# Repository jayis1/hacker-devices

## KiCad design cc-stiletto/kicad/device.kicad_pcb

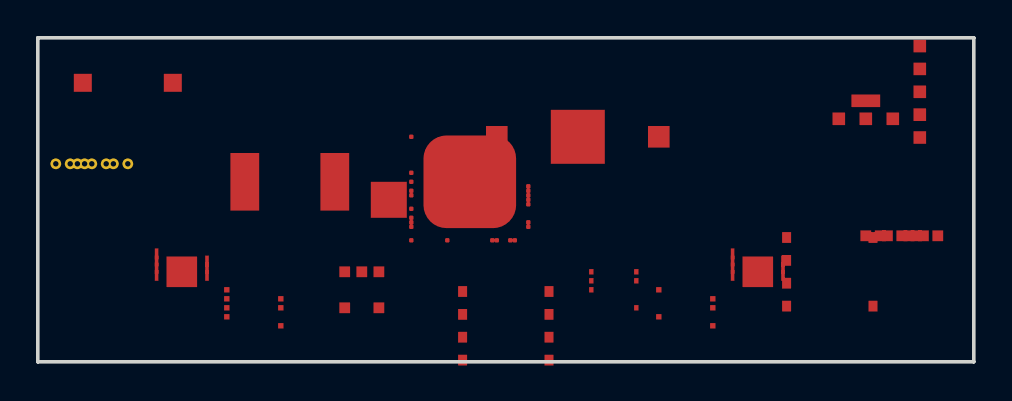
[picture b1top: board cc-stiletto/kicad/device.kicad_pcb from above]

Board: 0 copper layers, 52.0 x 18.0 mm, 17 parts (0 on the bottom side), 29 nets, no tracks yet.

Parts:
C_BULK: 100uF 50V; CP_Elec_6.3x7.7
D1: Status RGB LED; LED_RGB_1210
J1: USB-C Plug (victim/DUT); USB_C_Plug_Molex_105444
J2: USB-C Receptacle (source/host); USB_C_Receptacle_Amphenol_12401610E4-2A
J3: Pogo SWD debug; PinHeader_1x05_P1.27mm_Vertical
Q1: IPK95N04L; TO-263-3_TabPin2
R_SHUNT1: 5mR 1% 3W; R_2512_6332Metric
SW1: Mode/Hard-Reset button; SW_SPST_B3SN-6x6
U1: STM32G474CEU6; QFN-48-1EP_7x7mm_P0.5mm_EP5.15x5.15mm
U2, U3: FUSB302BMPX; QFN-14-1EP_3x3mm_P0.4mm_EP1.7x1.7mm
U4: LM5180-1W; SOT-23-6
U5: TPS25940; QFN-16-1EP_3x3mm_P0.5mm
U6: MAX5370; SOIC-14_3.9x8.7mm_P1.27mm
U7, U8: INA226; VSSOP-10_3x3mm_P0.5mm
U9: ISO1540; SOIC-8_3.9x4.9mm_P1.27mm

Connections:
BUTTON: SW1.1, U1.19
CC1_SNK: J2.A5, U3.2
CC1_SRC: J1.A5, U2.2
CC2_SNK: J2.B5, U3.3
CC2_SRC: J1.B5, U2.3
DAC_ILIM: U5.3, U6.2
GND: C_BULK.2, D1.4, J1.A1, J1.B1, J2.A1, J2.B1, J3.3, SW1.2, U1.5, U1.33, U1.EXP, U2.4, U2.14, U3.4, U3.14, U4.2, U4.5, U5.6, U6.7, U7.4, U8.4, U9.3, U9.6
HRTIM_CHA1: Q1.1, U1.29
I2C1_SCL: U1.42, U2.9
I2C1_SDA: U1.43, U2.8
I2C2_SDA: U1.30, U3.8
I2C3_SCL: U1.9, U6.6, U7.9, U8.9, U9.2, U9.8
I2C3_SDA: U1.10, U6.5, U7.8, U8.8, U9.1, U9.7
INT_SNK: U1.38, U3.10
INT_SRC: U1.20, U2.10
LED_B: D1.3, U1.16
LED_G: D1.2, U1.15
LED_R: D1.1, U1.14
NRST: J3.5, U1.7
SHUNT_SRC: J1.A4, J1.B4, R_SHUNT1.1, U7.2
SHUNT_SRC_OUT: R_SHUNT1.2, U5.1, U7.3
SWCLK: J3.2, U1.37
SWDIO: J3.1, U1.34
USB_DM: J1.A6, J2.A6, U1.46
USB_DP: J1.A7, J2.A7, U1.45
VBUS_SNK: J2.A4, J2.B4, Q1.2, U3.1, U5.2, U8.1
VBUS_SRC: C_BULK.1, Q1.3, U2.1, U4.1, U4.3, U7.1
VDD_3V3: J3.4, U1.1, U1.13, U6.14, U7.10, U8.10, U9.4
VDD_5V_ISO: U4.4, U9.5

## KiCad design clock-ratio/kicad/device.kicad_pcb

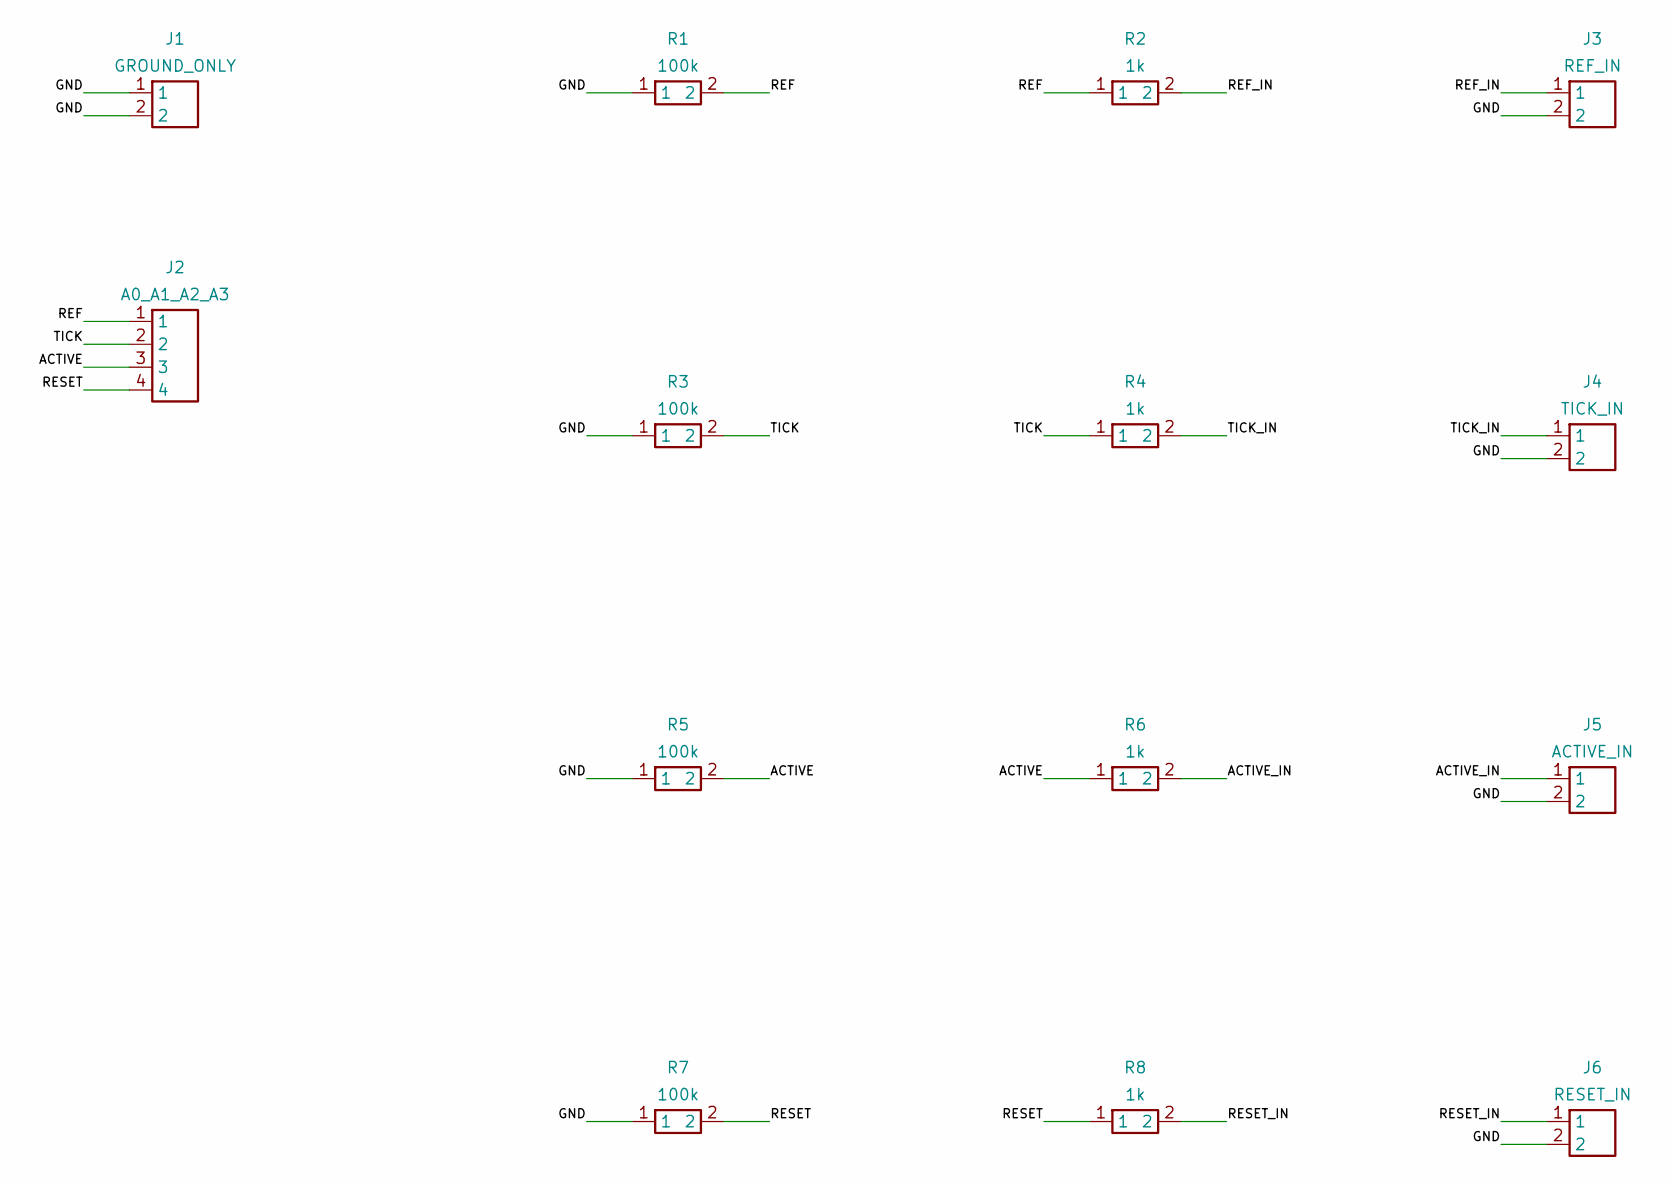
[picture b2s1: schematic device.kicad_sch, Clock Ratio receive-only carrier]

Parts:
J1: GROUND_ONLY; PinHeader_1x02_P2.54mm_Vertical
J2: A0_A1_A2_A3; PinHeader_1x04_P2.54mm_Vertical
J3: REF_IN; PinHeader_1x02_P2.54mm_Vertical
J4: TICK_IN; PinHeader_1x02_P2.54mm_Vertical
J5: ACTIVE_IN; PinHeader_1x02_P2.54mm_Vertical
J6: RESET_IN; PinHeader_1x02_P2.54mm_Vertical
R1, R3, R5, R7: 100k; R_Axial_DIN0207_L6.3mm_D2.5mm_P7.62mm_Horizontal
R2, R4, R6, R8: 1k; R_Axial_DIN0207_L6.3mm_D2.5mm_P7.62mm_Horizontal

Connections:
ACTIVE: J2.3, R5.2, R6.1
ACTIVE_IN: J5.1, R6.2
GND: J1.1, J1.2, J3.2, J4.2, J5.2, J6.2, R1.1, R3.1, R5.1, R7.1
REF: J2.1, R1.2, R2.1
REF_IN: J3.1, R2.2
RESET: J2.4, R7.2, R8.1
RESET_IN: J6.1, R8.2
TICK: J2.2, R3.2, R4.1
TICK_IN: J4.1, R4.2

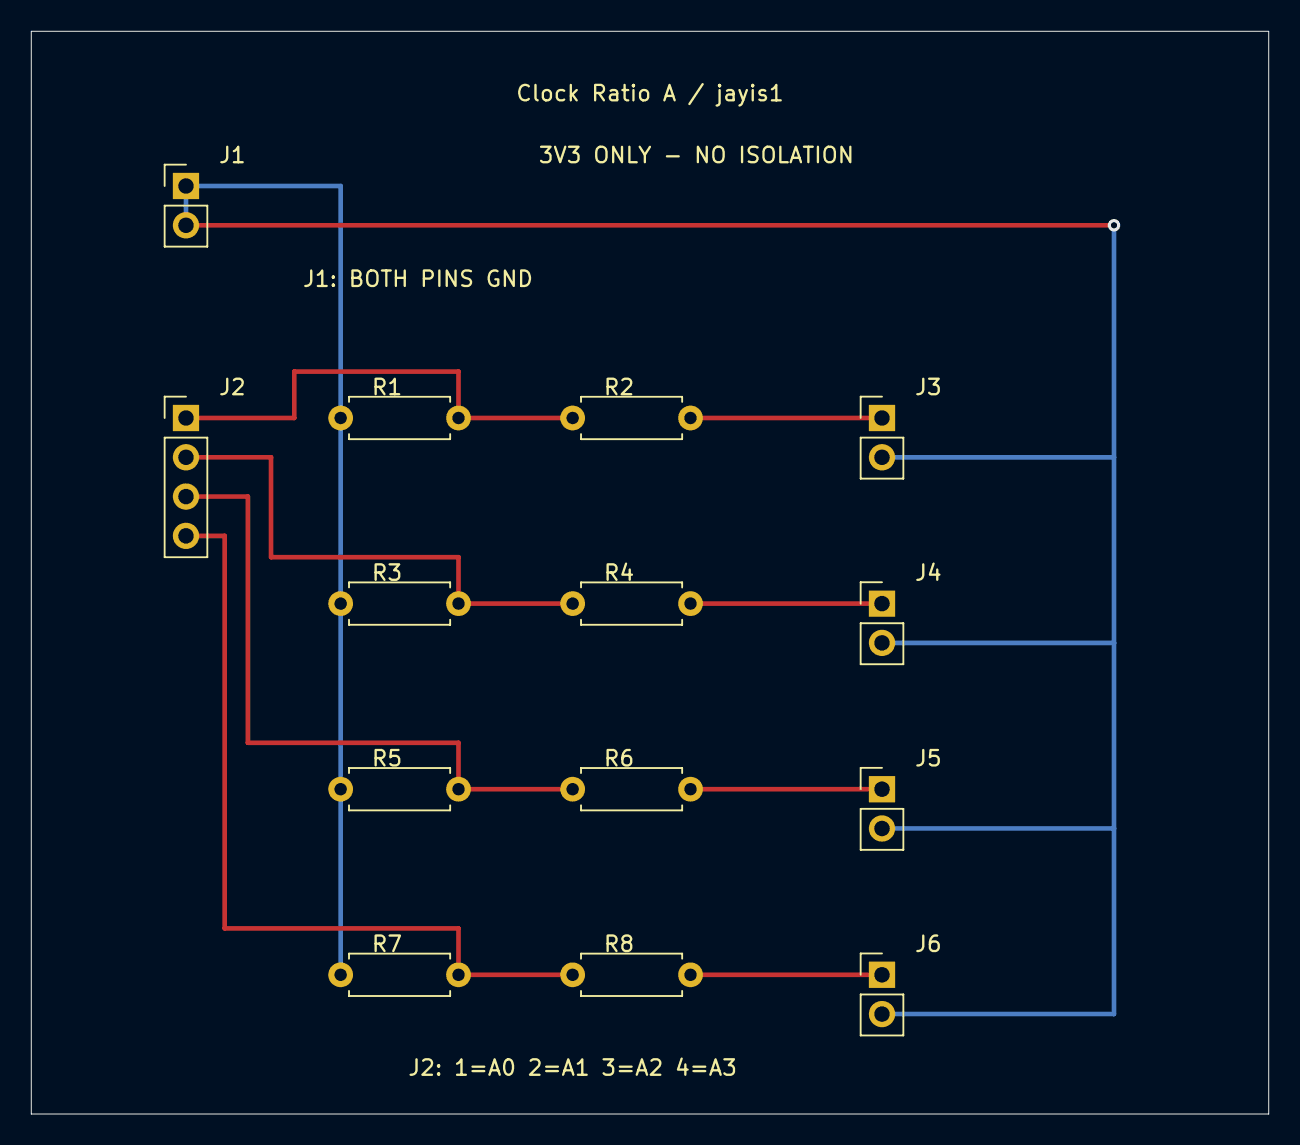
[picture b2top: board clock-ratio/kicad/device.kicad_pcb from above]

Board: 2 copper layers, 80.0 x 70.0 mm, 14 parts (0 on the bottom side), 9 nets.

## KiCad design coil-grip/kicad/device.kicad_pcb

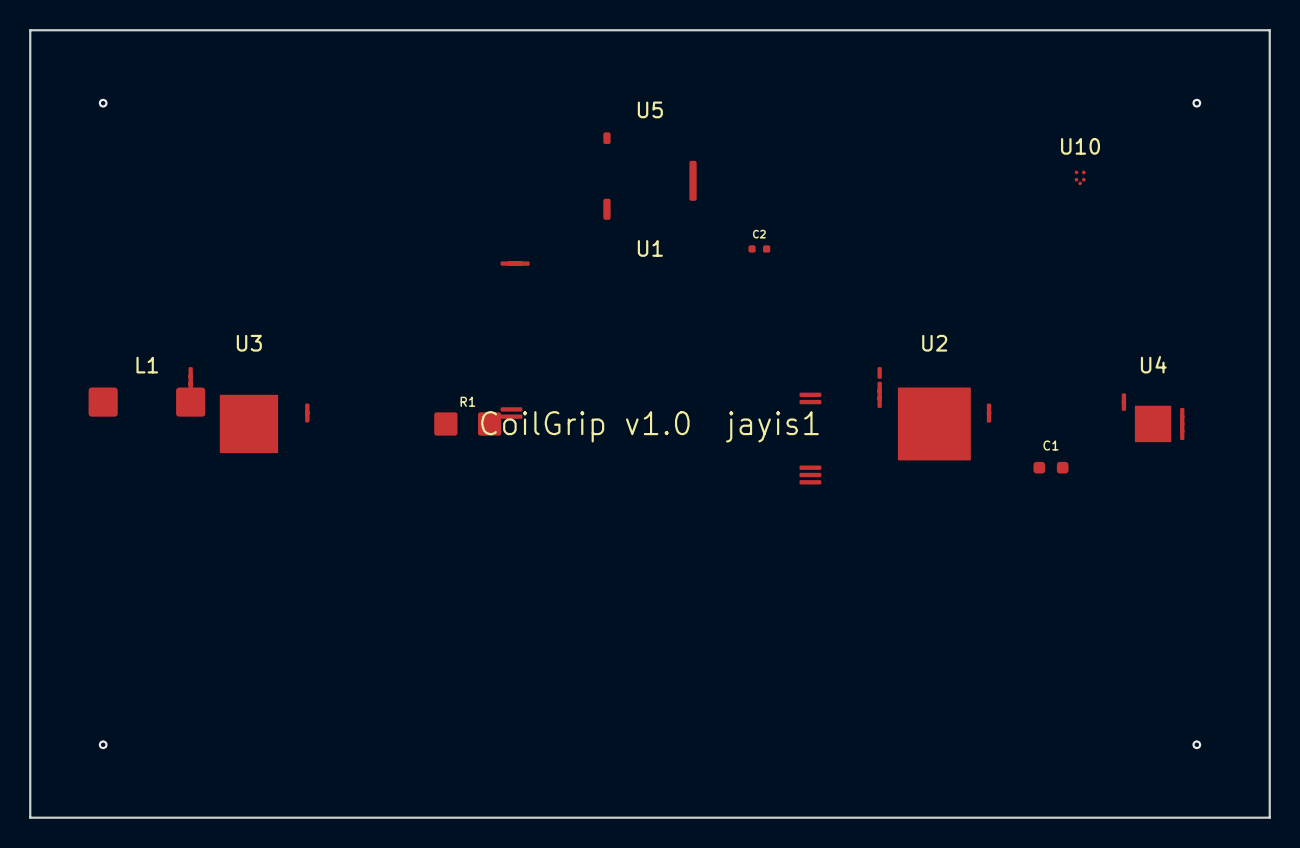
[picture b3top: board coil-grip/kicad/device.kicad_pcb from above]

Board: 4 copper layers, 85.0 x 54.0 mm, 10 parts (0 on the bottom side), 7 nets, no tracks yet.

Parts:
C1: 22nF; C_0603_1608Metric
C2: 100nF; C_0402_1005Metric
L1: 100uH; L_Wuerth_7447788101
R1: 10m; R_1206_3216Metric
U1: STM32H743ZIT6; LQFP-144_20x20mm_P0.5mm
U2: iCE40-UP5K-SG48; QFN-48-1EP_7x7mm_P0.5mm
U3: MWCT1011; LQFP-48_7x7mm_P0.5mm
U4: BQ51013B; QFN-20-1EP_4x4mm_P0.5mm
U5: ADS131M04; TSSOP-20_4.4x6.5mm_P0.65mm
U10: TMP117; DSBGA-6_1.5x1.5mm_P0.5mm

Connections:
+3V3: C2.1, U1.1, U1.13, U1.37, U3.45, U10.4
+5V: R1.1, U4.14, U5.17
GLITCH_FET_EN: U1.24, U2.25
GND: C1.2, C2.2, R1.2, U1.2, U1.12, U1.36, U2.48, U2.49, U3.46, U4.20, U5.1, U5.18, U10.5
LM_DRV: C1.1, U1.23, U2.26, U4.17
QI_TX_COIL_A: L1.1, U3.20
QI_TX_COIL_B: L1.2, U3.21

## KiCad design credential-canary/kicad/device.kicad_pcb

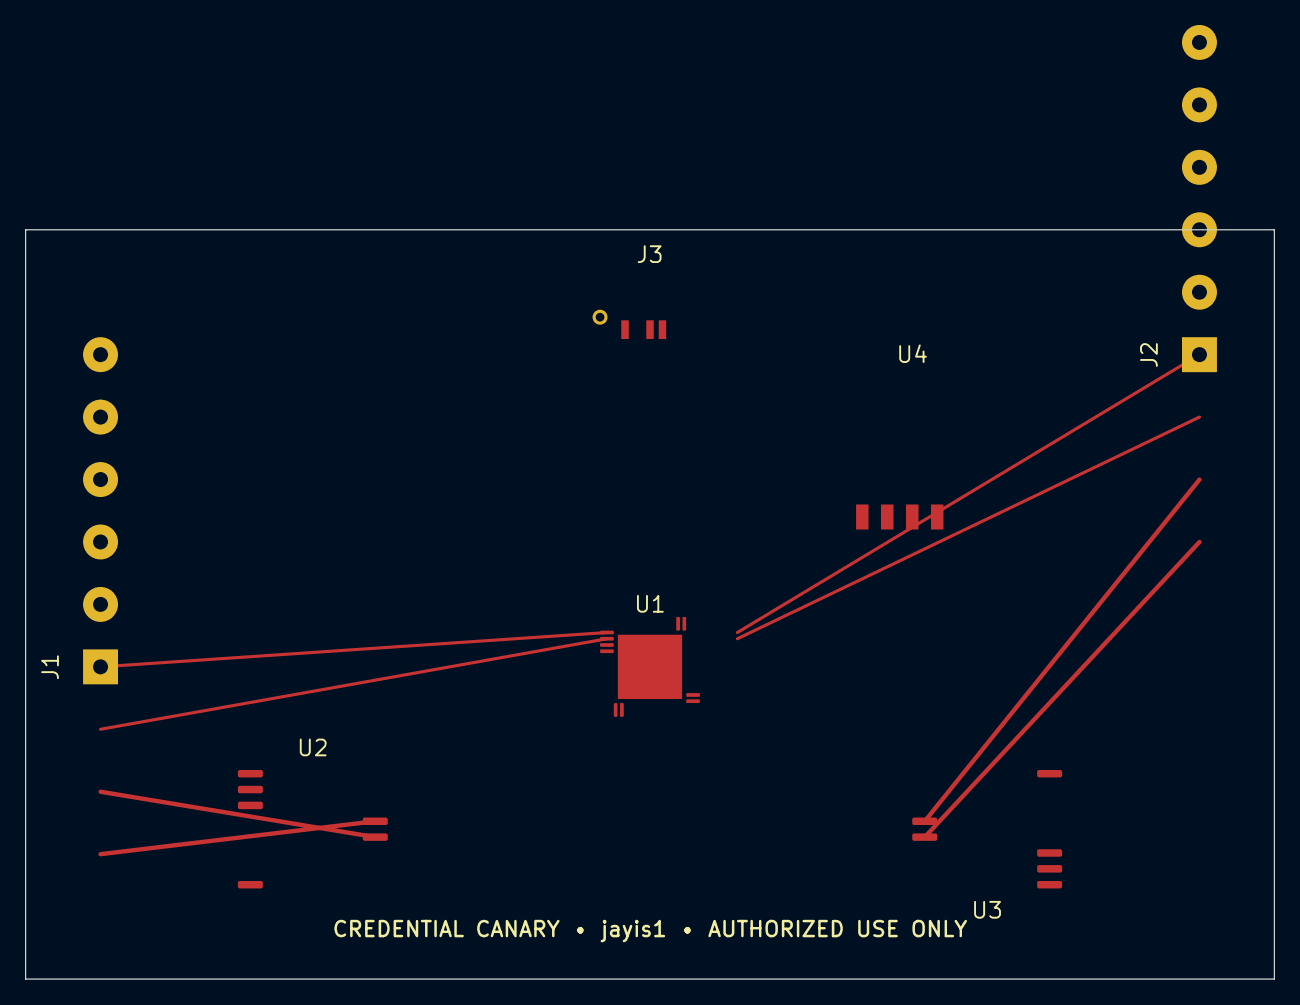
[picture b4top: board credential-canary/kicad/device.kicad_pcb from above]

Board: 2 copper layers, 100.0 x 60.0 mm, 7 parts (0 on the bottom side), 17 nets.

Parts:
J1: READER; TerminalBlock_Phoenix_MKDS-1,5-6_1x06_P5.00mm_Horizontal
J2: PANEL; TerminalBlock_Phoenix_MKDS-1,5-6_1x06_P5.00mm_Horizontal
J3: USB-C; USB_C_Receptacle_GCT_USB4105-xx-A_16P_TopMnt_Horizontal
U1: STM32G474CEU6; QFN-48-1EP_7x7mm_P0.5mm_EP5.15x5.15mm
U2, U3: ADM2483BRWZ; SOIC-16W_7.5x10.3mm_P1.27mm
U4: nRF52840; Raytac_MDBT50Q-1MV2

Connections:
+3V3: U2.1, U3.1, U4.2
BLE_RX: U1.26, U4.4
BLE_TX: U1.25, U4.3
GND: J1.5, J2.5, J3.A1, U1.49, U2.7, U3.7, U4.1
OSDP_P_A: J2.3, U3.12
OSDP_P_B: J2.4, U3.13
OSDP_R_A: J1.3, U2.12
OSDP_R_B: J1.4, U2.13
USART1_RX: U1.3, U2.3
USART1_TX: U1.4, U2.2
USART2_RX: U1.13, U3.3
USART2_TX: U1.14, U3.2
USB_DM: J3.A7, U1.38
USB_DP: J3.A6, U1.37
VBUS: J1.6, J2.6, J3.A4
WG_READER_D0: J1.1, U1.1
WG_READER_D1: J1.2, U1.2

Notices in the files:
cc-stiletto/kicad/device.kicad_pcb:
Copyright (c) 2026 jayis1 — authorized security research only
coil-grip/kicad/device.kicad_pcb:
SPDX-License-Identifier: GPL-2.0
